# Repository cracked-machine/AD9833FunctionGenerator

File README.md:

# DDS Function Generator
## Specification
- Produces sine, square, triange output
- Output waveform resolution of 0.1 Hz
- Frequency range: 1Hz - 100KHz
- Selectable ranges: 0-1KHz, 0-10KHz, 0-100KHz
- Frequency sweep mode with lower/upper range and speed control.
- Output amplitude up to 10 V peak-to-peak (+20dBv)
- DC offset voltage adjustable between -10V to +10V
- Output impedance of 600 Ω.

---

## Improved signal integrity at 100KHz
This is the square wave signal with +20dBv gain @ 10KHz

This is the same signal @ 100KHz. You can see the TL071 opamp (3MHz Unity GBP) is struggling to maintain the huge number of odd-integer harmonics of the waveform.

The LM7171 opamp (200MHz Unity GBP) is able to maintain the square wave harmonics for +20dBv @ 100KHz.  

---

## Schematic

[Schematic](https://github.com/cracked-machine/AD9833FunctionGenerator/blob/master/docs/Schematic/AD9833FunctionGenerator.pdf)

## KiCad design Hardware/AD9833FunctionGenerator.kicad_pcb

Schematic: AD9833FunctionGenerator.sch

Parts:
A1: Arduino_Nano_v3.x; Arduino_Nano
C1: 220nF; C_0805_2012Metric_Pad1.15x1.40mm_HandSolder
C2: 100nF; C_0805_2012Metric_Pad1.15x1.40mm_HandSolder
C_POTBP1: 100nF; C_0805_2012Metric_Pad1.15x1.40mm_HandSolder
J_AD9833: Conn_01x07; PinSocket_1x07_P2.54mm_Vertical
J_OUT1: Conn_01x02; PinSocket_1x02_P2.54mm_Vertical
J_PWR1: Conn_02x05_Odd_Even; PinHeader_2x05_P2.54mm_Vertical
ROFF1, ROFF2: 1K; R_0805_2012Metric_Pad1.15x1.40mm_HandSolder
RV_FREQ1: B10K; PTH901; MouserPartNo 652-PTH901-030S-103B
RV_TIME1: R_POT_Dual_Separate; PTH901
R_PHASE1: 100R; R_0805_2012Metric_Pad1.15x1.40mm_HandSolder
R_VEL1: 100R; R_0805_2012Metric_Pad1.15x1.40mm_HandSolder
SW_PWR1: SW_DPDT_x2; ALPS_SPUN191600
U1: LM7805_TO220; TO-220-3_Vertical; MouserPartNo 926-LM7805CT/NOPB
U_POT1: MCP42050; SOIC-14_3.9x8.7mm_P1.27mm; MouserPartNo 579-MCP42050-I/SL

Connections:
/5V: A1.30, C2.1, C_POTBP1.1, J_AD9833.2, ROFF1.2, RV_FREQ1.3, RV_FREQ1.6, RV_TIME1.1, RV_TIME1.4, U1.3, U_POT1.11 (~RS), U_POT1.12 (~SHDN), U_POT1.14 (VDD); also elsewhere on the board
/+12V: C1.1, SW_PWR1.1, U1.1; also elsewhere on the board
/-12V: SW_PWR1.4; also elsewhere on the board
/AREF: A1.17, A1.18
/DDS_CS: A1.13, J_AD9833.6
/DDS_REDUX: U_POT1.9 (PW0); also elsewhere on the board
/DDS_SIG: J_AD9833.7, U_POT1.8 (PA0)
/FREQHI: A1.19, RV_FREQ1.5
/FREQLO: A1.20, RV_FREQ1.2
/GND: A1.4, A1.29, C1.2, C2.2, C_POTBP1.2, J_AD9833.3, J_OUT1.2, J_PWR1.4, J_PWR1.6, J_PWR1.8, ROFF2.2, RV_FREQ1.1, RV_FREQ1.4, R_PHASE1.1, R_VEL1.1, U1.2, U_POT1.4 (VSS), U_POT1.10 (PB0); also elsewhere on the board
/MODEBTN: A1.6; also elsewhere on the board
/MOSI: A1.14, J_AD9833.4, U_POT1.3 (SI)
/OFFSETADJUST: U_POT1.6 (PW1); also elsewhere on the board
/OutputSection/SIGOUT: J_OUT1.1; also elsewhere on the board
/PHASE1: A1.22, RV_TIME1.5
/POT_CS: A1.12, U_POT1.1 (~CS)
/RANGEBTN: A1.8; also elsewhere on the board
/SCK: A1.16, J_AD9833.5, U_POT1.2 (SCK)
/SCL: A1.24; also elsewhere on the board
/SDA: A1.23; also elsewhere on the board
/VEL1: A1.25, RV_TIME1.2
/WAVEBTN: A1.5; also elsewhere on the board
unnamed: J_PWR1.2, SW_PWR1.2
unnamed: J_PWR1.10, SW_PWR1.5
unnamed: ROFF1.1, U_POT1.7 (PA1)
unnamed: ROFF2.1, U_POT1.5 (PB1)
unnamed: RV_TIME1.3, R_VEL1.2
unnamed: RV_TIME1.6, R_PHASE1.2

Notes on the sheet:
REF VCC GND DAT CLK FNC OUT
DDS Signal Generation
Output Amplifier Section
Power Supply Section
Peripheral Controls section
Signal Compensation
Micocontroller

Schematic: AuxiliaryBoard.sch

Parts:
J_AUX2MAIN2: Conn_02x05_Odd_Even; PinHeader_2x05_P2.54mm_Vertical
J_OLEDCONNECTOR1: Conn_01x04; PinSocket_1x04_P2.54mm_Vertical
R_FUNC1: 1K; R_0805_2012Metric_Pad1.15x1.40mm_HandSolder
R_MODE1: 1K; R_0805_2012Metric_Pad1.15x1.40mm_HandSolder
R_RANGE1: 1K; R_0805_2012Metric_Pad1.15x1.40mm_HandSolder
SW_FUNC1: SW_SPST; SW_PUSH_6mm; MouserPartNo 688-SKHHDJA010
SW_MODE1: SW_SPST; SW_PUSH_6mm; MouserPartNo 688-SKHHDJA010
SW_RANGE1: SW_SPST; SW_PUSH_6mm; MouserPartNo 688-SKHHDJA010

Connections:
/AuxiliaryBoard/5V_AUX: J_AUX2MAIN2.1, J_OLEDCONNECTOR1.1, SW_FUNC1.1, SW_MODE1.1, SW_RANGE1.1
/AuxiliaryBoard/GND_AUX: J_AUX2MAIN2.3, J_OLEDCONNECTOR1.2, R_FUNC1.1, R_MODE1.1, R_RANGE1.1
/AuxiliaryBoard/MODEBTN_AUX: J_AUX2MAIN2.7, R_MODE1.2, SW_MODE1.2
/AuxiliaryBoard/RANGEBTN_AUX: J_AUX2MAIN2.5, R_RANGE1.2, SW_RANGE1.2
/AuxiliaryBoard/SCL_AUX: J_AUX2MAIN2.8, J_OLEDCONNECTOR1.3
/AuxiliaryBoard/SDA_AUX: J_AUX2MAIN2.10, J_OLEDCONNECTOR1.4
/AuxiliaryBoard/WAVEBTN_AUX: J_AUX2MAIN2.9, R_FUNC1.2, SW_FUNC1.2

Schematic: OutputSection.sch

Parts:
CF2: 2pF; C_0805_2012Metric_Pad1.15x1.40mm_HandSolder
C_BUFFBP1, C_BUFFBP4: 2.2uF; C_0805_2012Metric_Pad1.15x1.40mm_HandSolder
C_BUFFBP2, C_BUFFBP3: 100nF; C_0805_2012Metric_Pad1.15x1.40mm_HandSolder
C_GAIN1: 470pF; C_0805_2012Metric_Pad1.15x1.40mm_HandSolder
C_MIXBP1, C_MIXBP4: 2.2uF; C_0805_2012Metric_Pad1.15x1.40mm_HandSolder
C_MIXBP2, C_MIXBP3: 100nF; C_0805_2012Metric_Pad1.15x1.40mm_HandSolder
RF1: 1k; R_0805_2012Metric_Pad1.15x1.40mm_HandSolder
RF2: 8K2; R_0805_2012Metric_Pad1.15x1.40mm_HandSolder
RG1: 1k; R_0805_2012Metric_Pad1.15x1.40mm_HandSolder
RV_AMP1: B10K; PTH901; MouserPartNo 652-PTH901-030S-103B
RV_LOWOFF1: 100K; Potentiometer_Piher_PT-6-V_Vertical; MouserPartNo 652-3296Y-1-104LF
RV_UPOFF1: 100K; Potentiometer_Piher_PT-6-V_Vertical; MouserPartNo 652-3296Y-1-104LF
R_HIOFF1: 1K; R_0805_2012Metric_Pad1.15x1.40mm_HandSolder
R_ISO1: 600R 1%; R_0805_2012Metric_Pad1.15x1.40mm_HandSolder
R_LOFF1: 1K; R_0805_2012Metric_Pad1.15x1.40mm_HandSolder
R_MIX1, R_MIX2, R_MIX3: 1K; R_0805_2012Metric_Pad1.15x1.40mm_HandSolder
TP_OFF1: TestPoint; TestPoint_Pad_D2.0mm
U_BUFF1: LM7171; SOIC-8_3.9x4.9mm_P1.27mm
U_MIX1: LM7171; SOIC-8_3.9x4.9mm_P1.27mm

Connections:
/+12V: C_BUFFBP1.1, C_BUFFBP2.1, C_MIXBP1.1, C_MIXBP2.1, R_HIOFF1.1, U_BUFF1.7, U_MIX1.7; also elsewhere on the board
/-12V: C_BUFFBP3.1, C_BUFFBP4.1, C_MIXBP3.1, C_MIXBP4.1, R_LOFF1.1, U_BUFF1.4, U_MIX1.4; also elsewhere on the board
/DDS_REDUX: U_BUFF1.3; also elsewhere on the board
/GND: C_BUFFBP1.2, C_BUFFBP2.2, C_BUFFBP3.2, C_BUFFBP4.2, C_GAIN1.2, C_MIXBP1.2, C_MIXBP2.2, C_MIXBP3.2, C_MIXBP4.2, RG1.1, U_MIX1.3; also elsewhere on the board
/OFFSETADJUST: R_MIX3.1; also elsewhere on the board
/OutputSection/SIGOUT: R_ISO1.1; also elsewhere on the board
unnamed 29: RF1.1, R_MIX1.1, U_BUFF1.6; also elsewhere on the board
unnamed 30: RF1.2, RG1.2, U_BUFF1.2; also elsewhere on the board
unnamed: CF2.1, RF2.1, R_ISO1.2, U_MIX1.6
unnamed: CF2.2, C_GAIN1.1, RF2.2, RV_AMP1.4, U_MIX1.2
unnamed: RV_AMP1.1, RV_UPOFF1.1, RV_UPOFF1.2
unnamed: RV_AMP1.2, R_MIX2.1, TP_OFF1.1
unnamed: RV_AMP1.3, RV_LOWOFF1.1, RV_LOWOFF1.2
unnamed: RV_AMP1.5, RV_AMP1.6, R_MIX1.2, R_MIX2.2, R_MIX3.2
unnamed: RV_LOWOFF1.3, R_LOFF1.2
unnamed: RV_UPOFF1.3, R_HIOFF1.2

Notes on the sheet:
User Offset
MCU Offset
User Gain

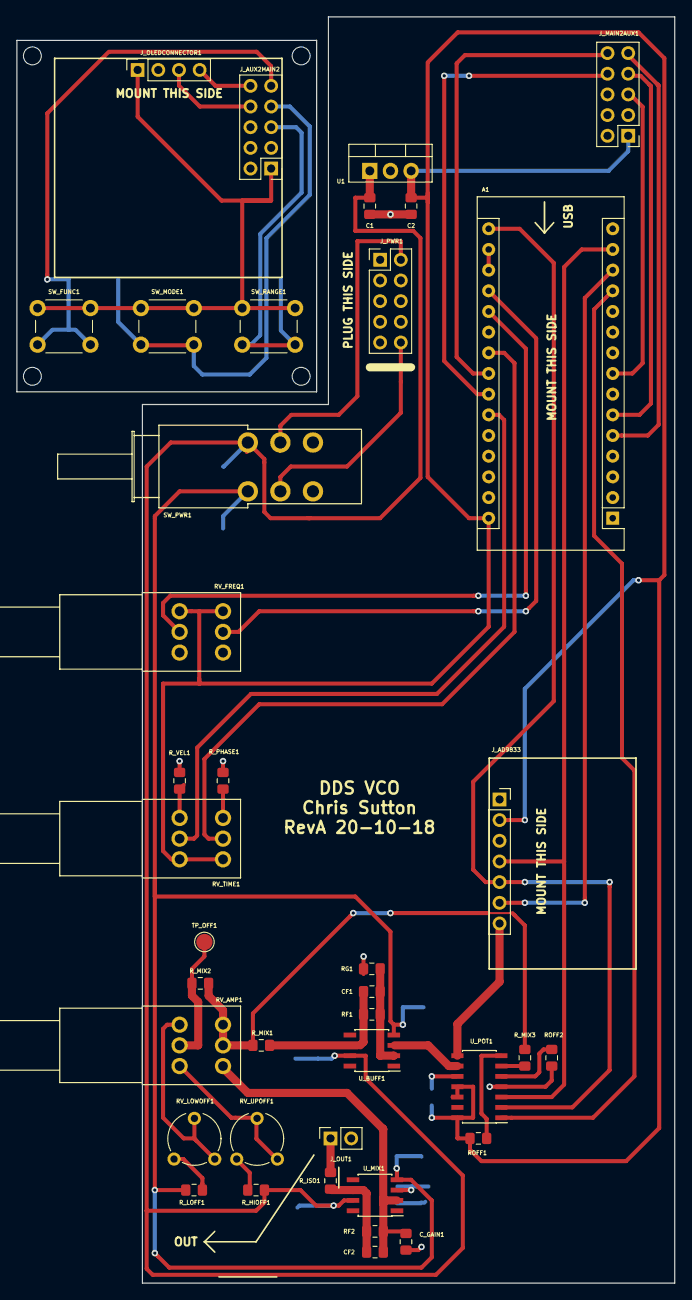
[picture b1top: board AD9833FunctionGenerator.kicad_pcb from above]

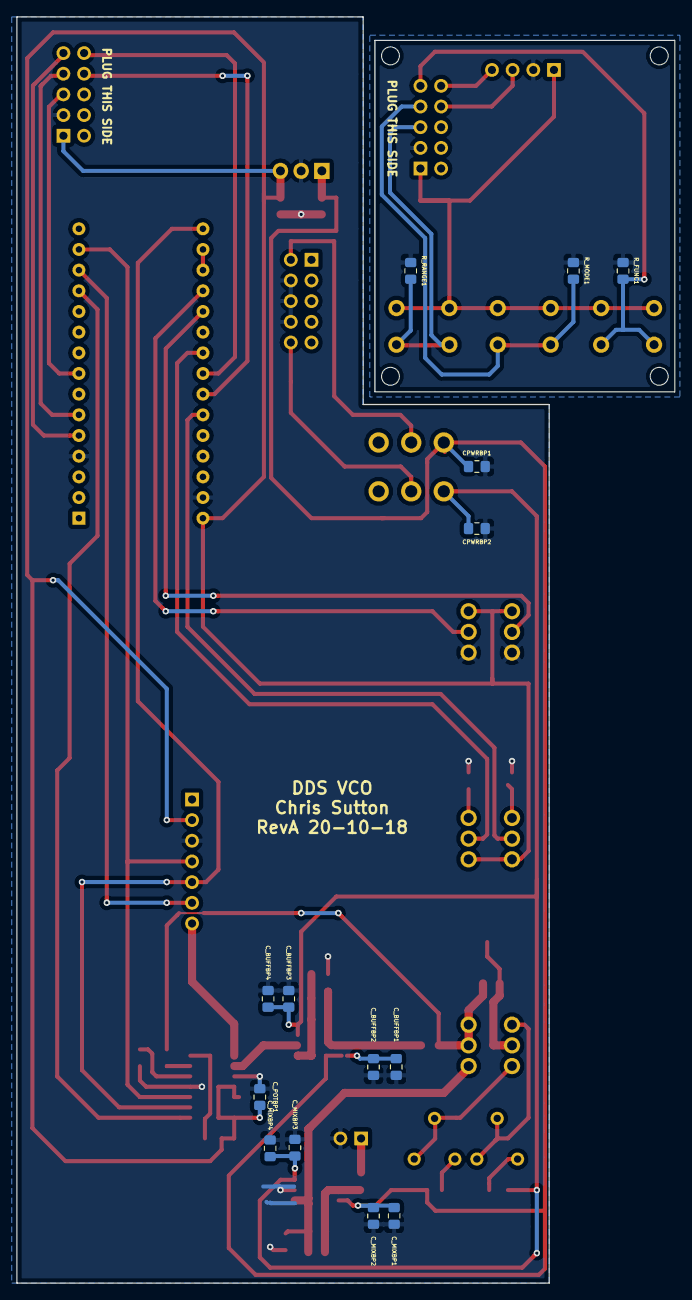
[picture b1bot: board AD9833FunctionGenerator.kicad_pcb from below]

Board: 2 copper layers, 80.8 x 155.6 mm, 53 parts (14 on the bottom side), 45 nets.

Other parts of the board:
CF1: 2pF; C_0805_2012Metric_Pad1.15x1.40mm_HandSolder
CPWRBP1, CPWRBP2: 100nF; C_0805_2012Metric_Pad1.15x1.40mm_HandSolder
J_MAIN2AUX1: Conn_02x05_Odd_Even; PinHeader_2x05_P2.54mm_Vertical

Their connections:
/5V: J_MAIN2AUX1.1; also elsewhere on the board
/+12V: CPWRBP1.1; also elsewhere on the board
/-12V: CPWRBP2.2; also elsewhere on the board
/GND: CPWRBP1.2, CPWRBP2.1, J_MAIN2AUX1.3; also elsewhere on the board
/MODEBTN: J_MAIN2AUX1.7; also elsewhere on the board
/RANGEBTN: J_MAIN2AUX1.5; also elsewhere on the board
/SCL: J_MAIN2AUX1.8; also elsewhere on the board
/SDA: J_MAIN2AUX1.10; also elsewhere on the board
/WAVEBTN: J_MAIN2AUX1.9; also elsewhere on the board
unnamed 29: CF1.1; also elsewhere on the board
unnamed 30: CF1.2; also elsewhere on the board

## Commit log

2018-09-03 updated software
    Added AD9833 Registers command construction
    Added BinaryUtils.h to aid binary string debugging.
2018-09-04 updated sw
2018-09-06 Updated Software
    -Fixed jitter (setwaveform every freq adjust)
    -Added sweep mode
    -Added velocity control for sweep mode (PCINT, needs to use ADCINT)
    -Added basic OLED output for func, hertz and velocity.
2018-09-24 updated sw
    - added five simultaneous ADC interrupts
    - added mode, freq and sweep info to display
    - added 7805 regulator for +/-12V and +5V rails.
2018-09-24 software updates
2018-09-27 fixed digpot/dds sidebyside spi config
2018-09-28 added attenuation and amplitude opamp circuit
2018-09-28 added analog output section for fixed gain compensation, variable offset and variable adjustments
2018-09-28 Board Layout completed
2018-09-29 Board Layout updated for potentiometer daughter boards
2018-09-29 changed to SMT. Added proper spaces for pots
2018-09-30 Changed to 4 layer board. Middle layers for 5V and GND. Signal traces on top layer, +/-12V and HF digital signals on bottom layer
2018-10-01 updated hardware
    - changed output opamp to inverting to allow 0V-20Vpp output
2018-10-01 save update
2018-10-02 Changed J_PWR1 from 01x03 to 02x05
2018-10-03 added MCP42050
2018-10-05 updated SW and HW
    - Added LM7171 output sectionz. 20Vp-p output, +26db gain, no cutoff up to 100KHz.
    - Corrected output section offset controls
    - Added phase control code (not working)
2018-10-06 updated HW
    - Changed Offset and Amp pots from 50K to 10: (better part availability)
    - Adjusted opamp gain resistors ratio
    - Added 100K trim pots for eaiser offset center adjustment
2018-10-07 Added custom opamp symbols
2018-10-07 updated hardware
2018-10-09 Created board layout RevB. Right-angled to front panel, with front facing aux board(OLED/Buttons)
2018-10-09 Tidied up schematic. Added sub-sheets
2018-10-10 updated HW
    - Added separate analog and digital ground to prevent output signal ripple/jitter
2018-10-11 updated HW (output section)
    - Switched VFA LM7171 for CFA LT1227 (improved frequency response)
    - Removed TL071 from output section
2018-10-13 board rev b
2018-10-14 updated board layout
2018-10-14 updated hardware
    - resized.relocated drill holes on aux board
    - removed keep out areas for SPI/I2C clock signals
    - Improved GND plane access for return signals
    - rmoved traces from underneath MCP42050
2018-10-15 Removed power traces from ground plane. improved horizontal component distribution. added right-angle PCB mount DPDT power switch.
2018-10-15 Updated potentimeter footprints
2018-10-16 Added third concentric dual pot for phase feature
2018-10-16 Updated footprints
2018-10-17 increased size of board layout to accomodate pot clearance.
2018-10-17 save
2018-10-17 Repositioned Nano module so that USB socket faces upwards
2018-10-18 Reduced size of board width to 90mm
2018-10-19 Refined board layout
2018-10-19 Draft RevA Board
2018-10-20 Final REVA
2018-10-20 refactored to 4U height
    Previous board layout form factor was slightly too large for 4U tolerances
2018-10-20 updated board layout description
2018-10-20 added 3D render
2018-10-26 firmware updates
2018-10-26 created front panel
2018-12-05 Created AS7 software project
2018-12-05 Imported Arduino sketch to AS7
2018-12-06 restructured main function
2018-12-06 Reverting to the state of the project at 84a95b68ddf844441da620dbd90f4e540ebd8817
2018-12-06 update test
